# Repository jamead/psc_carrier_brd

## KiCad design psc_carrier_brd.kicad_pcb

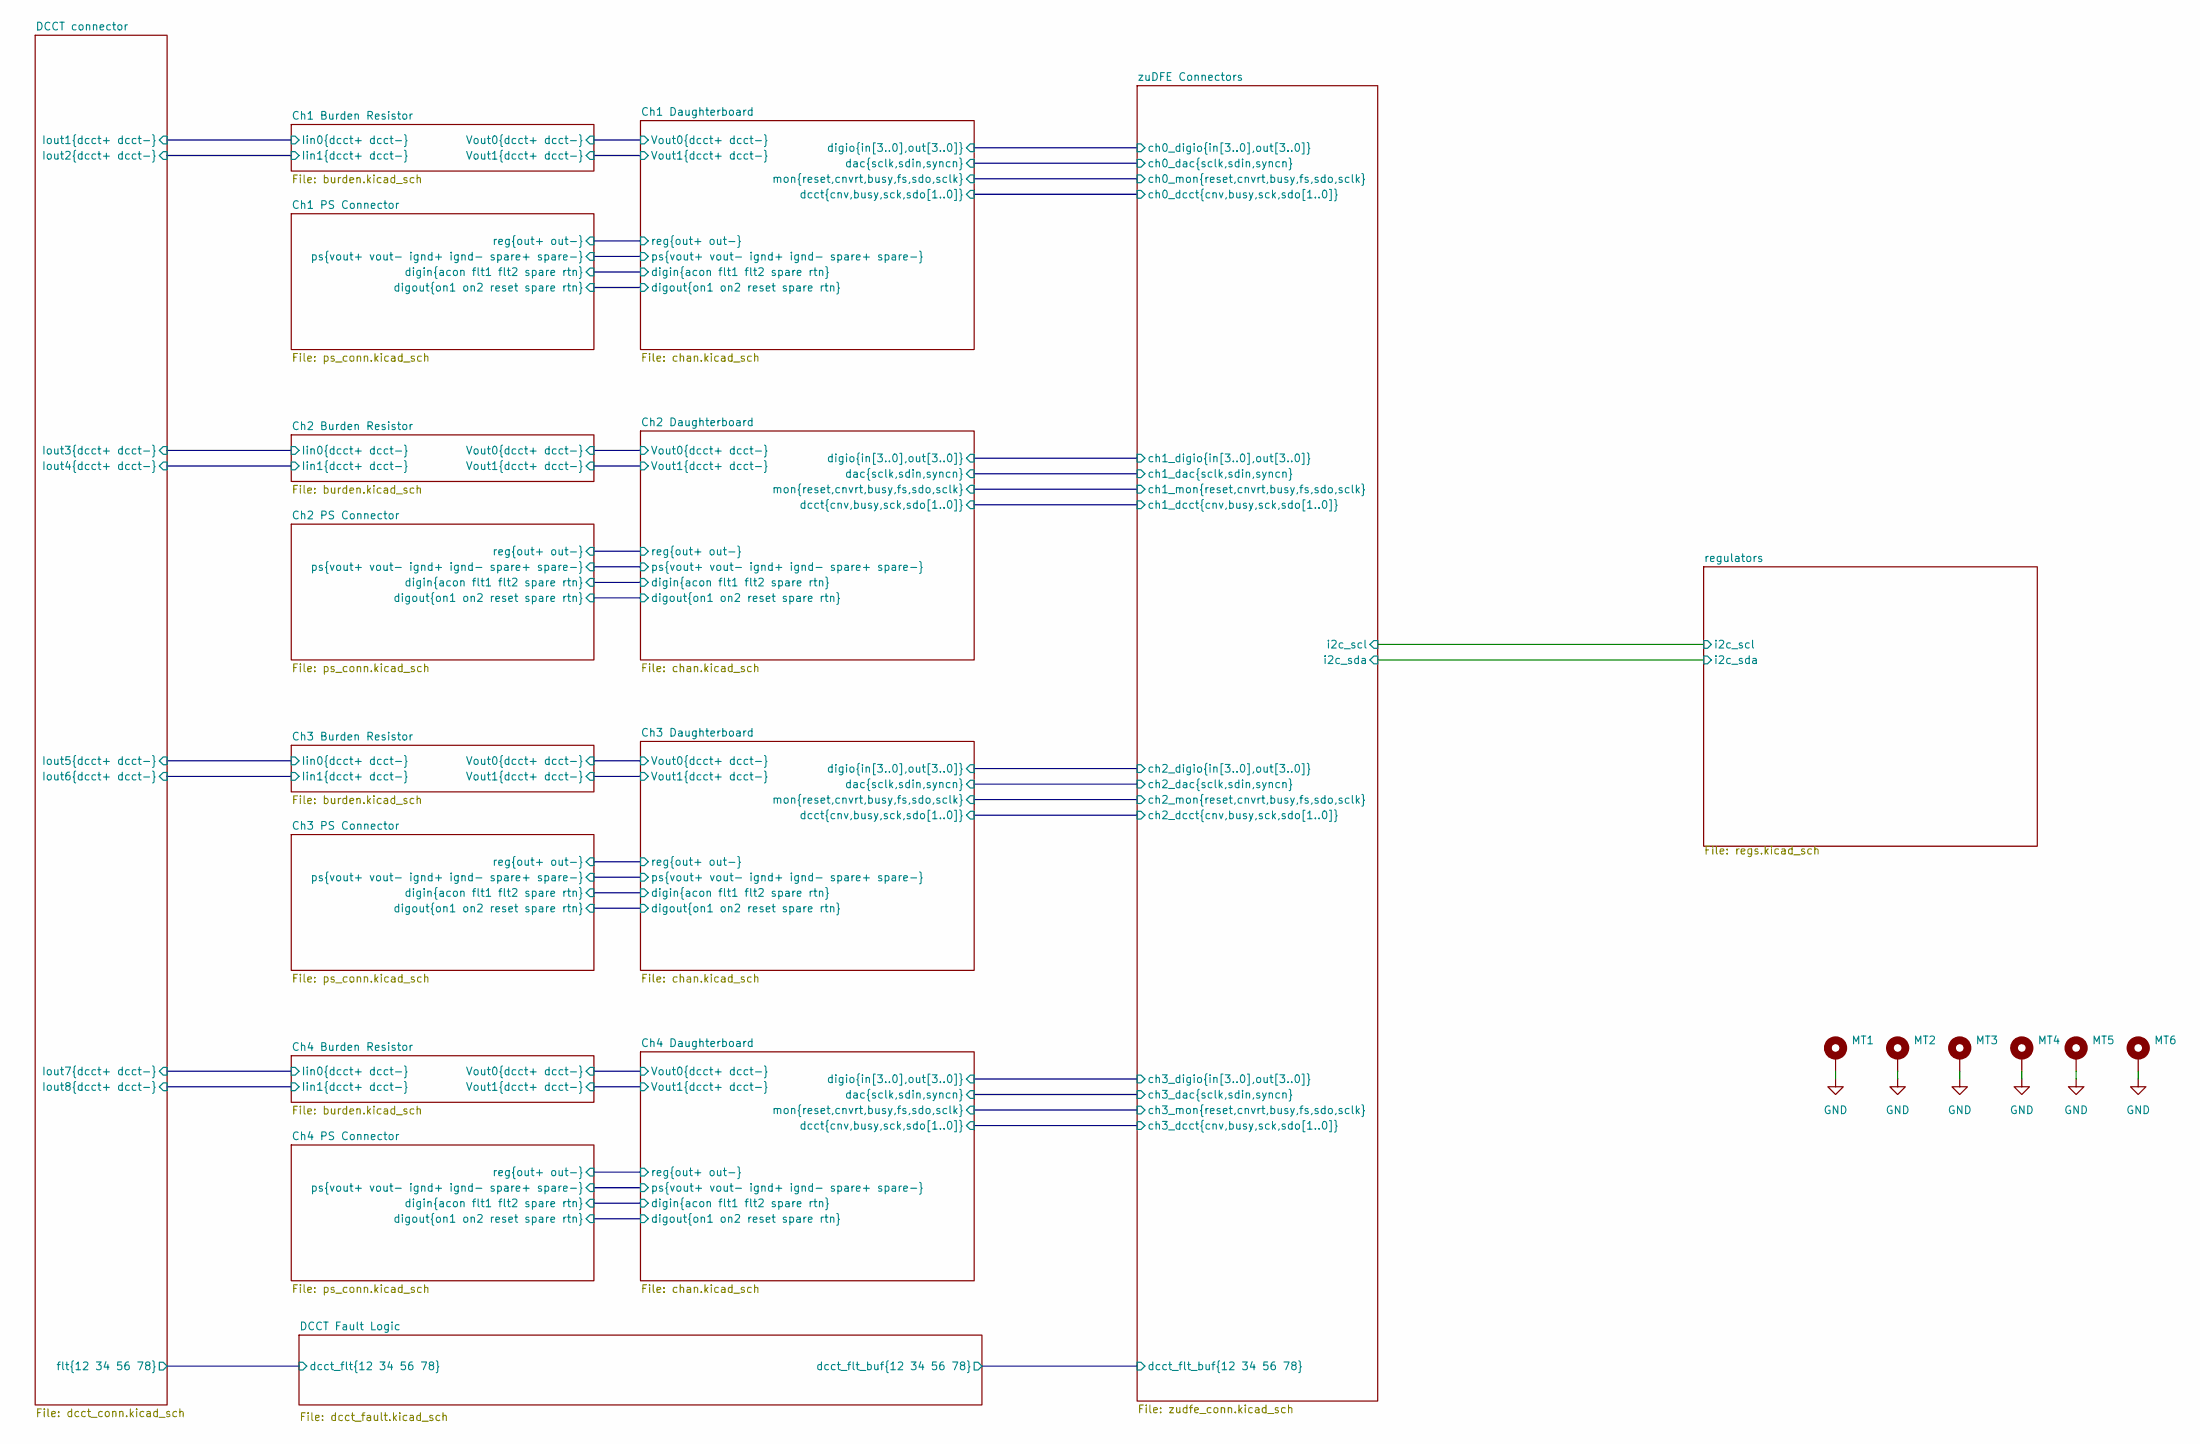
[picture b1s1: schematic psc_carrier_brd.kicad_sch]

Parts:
MT1, MT2, MT3, MT4, MT5, MT6: MountingHole_Pad; MountingHole_4.3mm_M4_DIN965_Pad

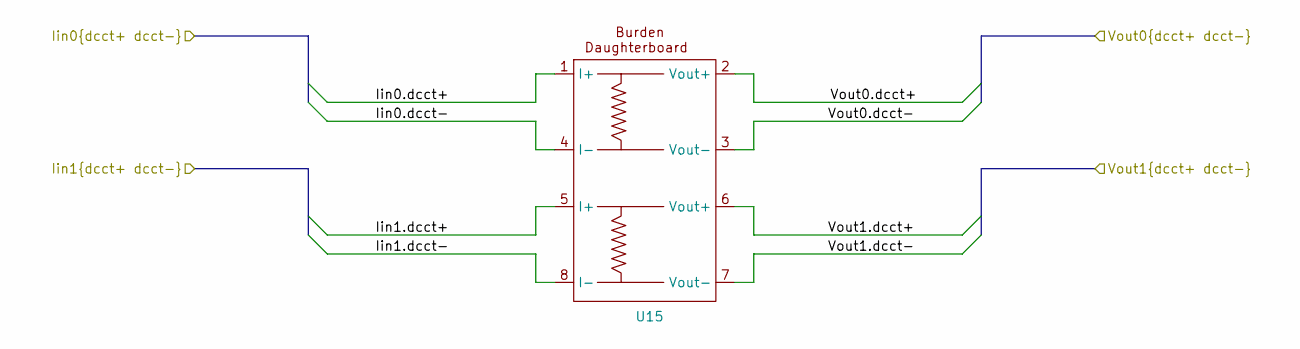
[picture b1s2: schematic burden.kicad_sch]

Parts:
U15: burden

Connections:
/Ch1 Burden Resistor/Iin0.dcct-: U15.4 (I-); also elsewhere on the board

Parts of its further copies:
U16, U17, U18: burden

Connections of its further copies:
/Ch2 Burden Resistor/Iin0.dcct+: U16.1 (I+); also elsewhere on the board
/Ch2 Burden Resistor/Iin0.dcct-: U16.4 (I-); also elsewhere on the board
/Ch2 Burden Resistor/Iin1.dcct+: U16.5 (I+); also elsewhere on the board
/Ch2 Burden Resistor/Iin1.dcct-: U16.8 (I-); also elsewhere on the board
/Ch2 Burden Resistor/Vout0.dcct+: U16.2 (Vout+); also elsewhere on the board
/Ch2 Burden Resistor/Vout0.dcct-: U16.3 (Vout-); also elsewhere on the board
/Ch2 Burden Resistor/Vout1.dcct+: U16.6 (Vout+); also elsewhere on the board
/Ch2 Burden Resistor/Vout1.dcct-: U16.7 (Vout-); also elsewhere on the board
/Ch3 Burden Resistor/Iin0.dcct+: U17.1 (I+); also elsewhere on the board
/Ch3 Burden Resistor/Iin0.dcct-: U17.4 (I-); also elsewhere on the board
/Ch3 Burden Resistor/Iin1.dcct+: U17.5 (I+); also elsewhere on the board
/Ch3 Burden Resistor/Iin1.dcct-: U17.8 (I-); also elsewhere on the board
/Ch3 Burden Resistor/Vout0.dcct+: U17.2 (Vout+); also elsewhere on the board
/Ch3 Burden Resistor/Vout0.dcct-: U17.3 (Vout-); also elsewhere on the board
/Ch3 Burden Resistor/Vout1.dcct+: U17.6 (Vout+); also elsewhere on the board
/Ch3 Burden Resistor/Vout1.dcct-: U17.7 (Vout-); also elsewhere on the board
/Ch4 Burden Resistor/Iin0.dcct+: U18.1 (I+); also elsewhere on the board
/Ch4 Burden Resistor/Iin0.dcct-: U18.4 (I-); also elsewhere on the board
/Ch4 Burden Resistor/Iin1.dcct+: U18.5 (I+); also elsewhere on the board
/Ch4 Burden Resistor/Iin1.dcct-: U18.8 (I-); also elsewhere on the board
/Ch4 Burden Resistor/Vout0.dcct+: U18.2 (Vout+); also elsewhere on the board
/Ch4 Burden Resistor/Vout0.dcct-: U18.3 (Vout-); also elsewhere on the board
/Ch4 Burden Resistor/Vout1.dcct+: U18.6 (Vout+); also elsewhere on the board
/Ch4 Burden Resistor/Vout1.dcct-: U18.7 (Vout-); also elsewhere on the board

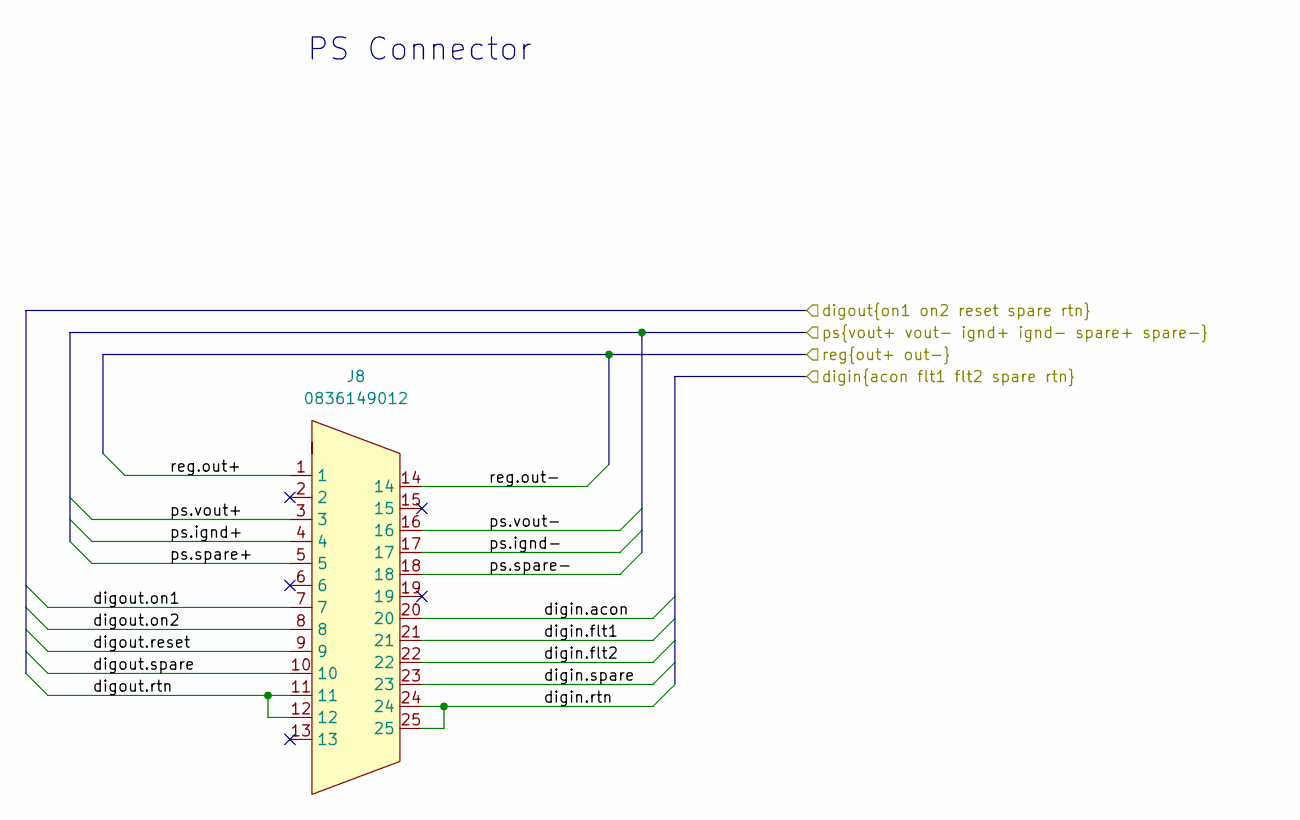
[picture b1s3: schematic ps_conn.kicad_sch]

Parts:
J8: 0836149012

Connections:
/Ch1 Daughterboard/digin.acon: J8.20; also elsewhere on the board
/Ch1 Daughterboard/digin.flt1: J8.21; also elsewhere on the board
/Ch1 Daughterboard/digin.flt2: J8.22; also elsewhere on the board
/Ch1 Daughterboard/digin.rtn: J8.24, J8.25; also elsewhere on the board
/Ch1 Daughterboard/digin.spare: J8.23; also elsewhere on the board
/Ch1 Daughterboard/digout.on1: J8.7; also elsewhere on the board
/Ch1 Daughterboard/digout.on2: J8.8; also elsewhere on the board
/Ch1 Daughterboard/digout.reset: J8.9; also elsewhere on the board
/Ch1 Daughterboard/digout.rtn: J8.11, J8.12; also elsewhere on the board
/Ch1 Daughterboard/digout.spare: J8.10; also elsewhere on the board
/Ch1 Daughterboard/ps.ignd+: J8.4; also elsewhere on the board
/Ch1 Daughterboard/ps.ignd-: J8.17; also elsewhere on the board
/Ch1 Daughterboard/ps.spare+: J8.5; also elsewhere on the board
/Ch1 Daughterboard/ps.spare-: J8.18; also elsewhere on the board
/Ch1 Daughterboard/ps.vout+: J8.3; also elsewhere on the board
/Ch1 Daughterboard/ps.vout-: J8.16; also elsewhere on the board
/Ch1 Daughterboard/reg.out+: J8.1; also elsewhere on the board
/Ch1 Daughterboard/reg.out-: J8.14; also elsewhere on the board

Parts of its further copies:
J11, J14, J17: 0836149012

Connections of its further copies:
/Ch2 Daughterboard/digin.acon: J11.20; also elsewhere on the board
/Ch2 Daughterboard/digin.flt1: J11.21; also elsewhere on the board
/Ch2 Daughterboard/digin.flt2: J11.22; also elsewhere on the board
/Ch2 Daughterboard/digin.rtn: J11.24, J11.25; also elsewhere on the board
/Ch2 Daughterboard/digin.spare: J11.23; also elsewhere on the board
/Ch2 Daughterboard/digout.on1: J11.7; also elsewhere on the board
/Ch2 Daughterboard/digout.on2: J11.8; also elsewhere on the board
/Ch2 Daughterboard/digout.reset: J11.9; also elsewhere on the board
/Ch2 Daughterboard/digout.rtn: J11.11, J11.12; also elsewhere on the board
/Ch2 Daughterboard/digout.spare: J11.10; also elsewhere on the board
/Ch2 Daughterboard/ps.ignd+: J11.4; also elsewhere on the board
/Ch2 Daughterboard/ps.ignd-: J11.17; also elsewhere on the board
/Ch2 Daughterboard/ps.spare+: J11.5; also elsewhere on the board
/Ch2 Daughterboard/ps.spare-: J11.18; also elsewhere on the board
/Ch2 Daughterboard/ps.vout+: J11.3; also elsewhere on the board
/Ch2 Daughterboard/ps.vout-: J11.16; also elsewhere on the board
/Ch2 Daughterboard/reg.out+: J11.1; also elsewhere on the board
/Ch2 Daughterboard/reg.out-: J11.14; also elsewhere on the board
/Ch3 Daughterboard/digin.acon: J14.20; also elsewhere on the board
/Ch3 Daughterboard/digin.flt1: J14.21; also elsewhere on the board
/Ch3 Daughterboard/digin.flt2: J14.22; also elsewhere on the board
/Ch3 Daughterboard/digin.rtn: J14.24, J14.25; also elsewhere on the board
/Ch3 Daughterboard/digin.spare: J14.23; also elsewhere on the board
/Ch3 Daughterboard/digout.on1: J14.7; also elsewhere on the board
/Ch3 Daughterboard/digout.on2: J14.8; also elsewhere on the board
/Ch3 Daughterboard/digout.reset: J14.9; also elsewhere on the board
/Ch3 Daughterboard/digout.rtn: J14.11, J14.12; also elsewhere on the board
/Ch3 Daughterboard/digout.spare: J14.10; also elsewhere on the board
/Ch3 Daughterboard/ps.ignd+: J14.4; also elsewhere on the board
/Ch3 Daughterboard/ps.ignd-: J14.17; also elsewhere on the board
/Ch3 Daughterboard/ps.spare+: J14.5; also elsewhere on the board
/Ch3 Daughterboard/ps.spare-: J14.18; also elsewhere on the board
/Ch3 Daughterboard/ps.vout+: J14.3; also elsewhere on the board
/Ch3 Daughterboard/ps.vout-: J14.16; also elsewhere on the board
/Ch3 Daughterboard/reg.out+: J14.1; also elsewhere on the board
/Ch3 Daughterboard/reg.out-: J14.14; also elsewhere on the board
/Ch4 Daughterboard/digin.acon: J17.20; also elsewhere on the board
/Ch4 Daughterboard/digin.flt1: J17.21; also elsewhere on the board
/Ch4 Daughterboard/digin.flt2: J17.22; also elsewhere on the board
/Ch4 Daughterboard/digin.rtn: J17.24, J17.25; also elsewhere on the board
/Ch4 Daughterboard/digin.spare: J17.23; also elsewhere on the board
/Ch4 Daughterboard/digout.on1: J17.7; also elsewhere on the board
/Ch4 Daughterboard/digout.on2: J17.8; also elsewhere on the board
/Ch4 Daughterboard/digout.reset: J17.9; also elsewhere on the board
/Ch4 Daughterboard/digout.rtn: J17.11, J17.12; also elsewhere on the board
/Ch4 Daughterboard/digout.spare: J17.10; also elsewhere on the board
/Ch4 Daughterboard/ps.ignd+: J17.4; also elsewhere on the board
/Ch4 Daughterboard/ps.ignd-: J17.17; also elsewhere on the board
/Ch4 Daughterboard/ps.spare+: J17.5; also elsewhere on the board
/Ch4 Daughterboard/ps.spare-: J17.18; also elsewhere on the board
/Ch4 Daughterboard/ps.vout+: J17.3; also elsewhere on the board
/Ch4 Daughterboard/ps.vout-: J17.16; also elsewhere on the board
/Ch4 Daughterboard/reg.out+: J17.1; also elsewhere on the board
/Ch4 Daughterboard/reg.out-: J17.14; also elsewhere on the board

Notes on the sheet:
PS Connector

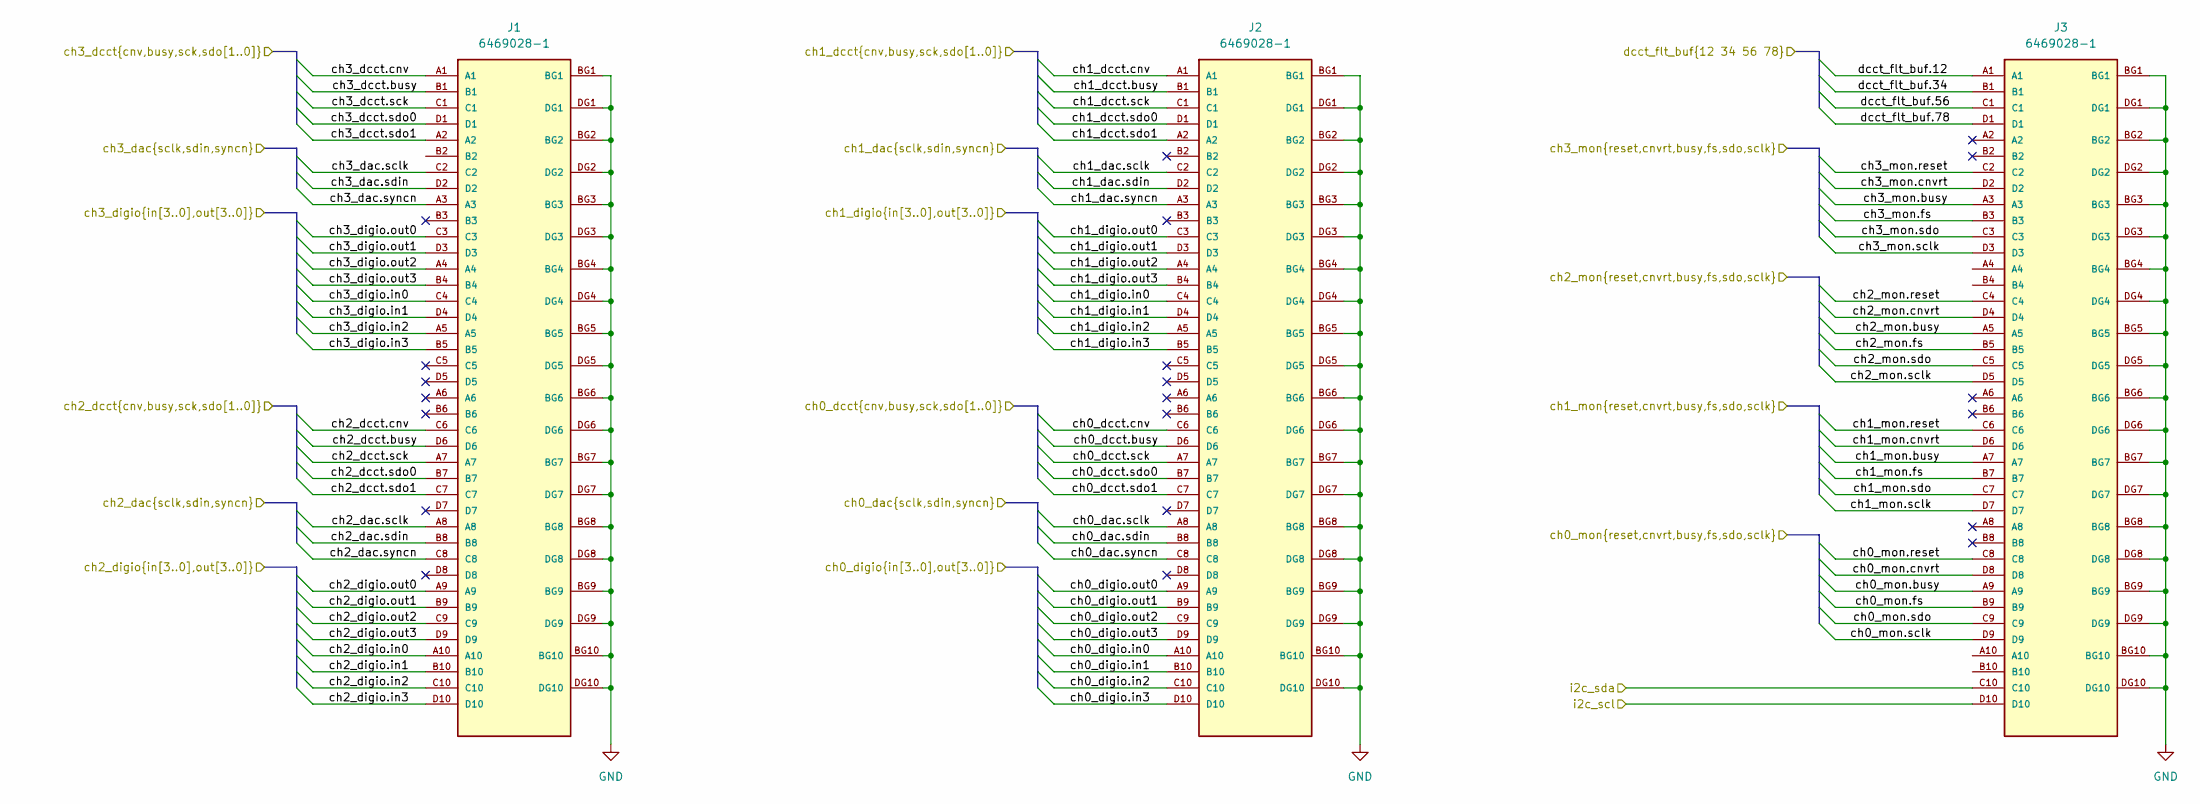
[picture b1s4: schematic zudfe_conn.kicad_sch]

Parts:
J1, J2, J3: 6469028-1; TE_6469028-1; PARTREV E

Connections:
/Ch1 Daughterboard/dac.sclk: J2.A8; also elsewhere on the board
/Ch1 Daughterboard/dac.sdin: J2.B8; also elsewhere on the board
/Ch1 Daughterboard/dac.syncn: J2.C8; also elsewhere on the board
/Ch1 Daughterboard/dcct.busy: J2.D6; also elsewhere on the board
/Ch1 Daughterboard/dcct.cnv: J2.C6; also elsewhere on the board
/Ch1 Daughterboard/dcct.sck: J2.A7; also elsewhere on the board
/Ch1 Daughterboard/dcct.sdo0: J2.B7; also elsewhere on the board
/Ch1 Daughterboard/dcct.sdo1: J2.C7; also elsewhere on the board
/Ch1 Daughterboard/digio.in0: J2.A10; also elsewhere on the board
/Ch1 Daughterboard/digio.in1: J2.B10; also elsewhere on the board
/Ch1 Daughterboard/digio.in2: J2.C10; also elsewhere on the board
/Ch1 Daughterboard/digio.in3: J2.D10; also elsewhere on the board
/Ch1 Daughterboard/digio.out0: J2.A9; also elsewhere on the board
/Ch1 Daughterboard/digio.out1: J2.B9; also elsewhere on the board
/Ch1 Daughterboard/digio.out2: J2.C9; also elsewhere on the board
/Ch1 Daughterboard/digio.out3: J2.D9; also elsewhere on the board
/Ch1 Daughterboard/mon.busy: J3.A9; also elsewhere on the board
/Ch1 Daughterboard/mon.cnvrt: J3.D8; also elsewhere on the board
/Ch1 Daughterboard/mon.fs: J3.B9; also elsewhere on the board
/Ch1 Daughterboard/mon.reset: J3.C8; also elsewhere on the board
/Ch1 Daughterboard/mon.sclk: J3.D9; also elsewhere on the board
/Ch1 Daughterboard/mon.sdo: J3.C9; also elsewhere on the board
/Ch2 Daughterboard/dac.sclk: J2.C2; also elsewhere on the board
/Ch2 Daughterboard/dac.sdin: J2.D2; also elsewhere on the board
/Ch2 Daughterboard/dac.syncn: J2.A3; also elsewhere on the board
/Ch2 Daughterboard/dcct.busy: J2.B1; also elsewhere on the board
/Ch2 Daughterboard/dcct.cnv: J2.A1; also elsewhere on the board
/Ch2 Daughterboard/dcct.sck: J2.C1; also elsewhere on the board
/Ch2 Daughterboard/dcct.sdo0: J2.D1; also elsewhere on the board
/Ch2 Daughterboard/dcct.sdo1: J2.A2; also elsewhere on the board
/Ch2 Daughterboard/digio.in0: J2.C4; also elsewhere on the board
/Ch2 Daughterboard/digio.in1: J2.D4; also elsewhere on the board
/Ch2 Daughterboard/digio.in2: J2.A5; also elsewhere on the board
/Ch2 Daughterboard/digio.in3: J2.B5; also elsewhere on the board
/Ch2 Daughterboard/digio.out0: J2.C3; also elsewhere on the board
/Ch2 Daughterboard/digio.out1: J2.D3; also elsewhere on the board
/Ch2 Daughterboard/digio.out2: J2.A4; also elsewhere on the board
/Ch2 Daughterboard/digio.out3: J2.B4; also elsewhere on the board
/Ch2 Daughterboard/mon.busy: J3.A7; also elsewhere on the board
/Ch2 Daughterboard/mon.cnvrt: J3.D6; also elsewhere on the board
/Ch2 Daughterboard/mon.fs: J3.B7; also elsewhere on the board
/Ch2 Daughterboard/mon.reset: J3.C6; also elsewhere on the board
/Ch2 Daughterboard/mon.sclk: J3.D7; also elsewhere on the board
/Ch2 Daughterboard/mon.sdo: J3.C7; also elsewhere on the board
/Ch3 Daughterboard/dac.sclk: J1.A8; also elsewhere on the board
/Ch3 Daughterboard/dac.sdin: J1.B8; also elsewhere on the board
/Ch3 Daughterboard/dac.syncn: J1.C8; also elsewhere on the board
/Ch3 Daughterboard/dcct.busy: J1.D6; also elsewhere on the board
/Ch3 Daughterboard/dcct.cnv: J1.C6; also elsewhere on the board
/Ch3 Daughterboard/dcct.sck: J1.A7; also elsewhere on the board
/Ch3 Daughterboard/dcct.sdo0: J1.B7; also elsewhere on the board
/Ch3 Daughterboard/dcct.sdo1: J1.C7; also elsewhere on the board
/Ch3 Daughterboard/digio.in0: J1.A10; also elsewhere on the board
/Ch3 Daughterboard/digio.in1: J1.B10; also elsewhere on the board
/Ch3 Daughterboard/digio.in2: J1.C10; also elsewhere on the board
/Ch3 Daughterboard/digio.in3: J1.D10; also elsewhere on the board
/Ch3 Daughterboard/digio.out0: J1.A9; also elsewhere on the board
/Ch3 Daughterboard/digio.out1: J1.B9; also elsewhere on the board
/Ch3 Daughterboard/digio.out2: J1.C9; also elsewhere on the board
/Ch3 Daughterboard/digio.out3: J1.D9; also elsewhere on the board
/Ch3 Daughterboard/mon.busy: J3.A5; also elsewhere on the board
/Ch3 Daughterboard/mon.cnvrt: J3.D4; also elsewhere on the board
/Ch3 Daughterboard/mon.fs: J3.B5; also elsewhere on the board
/Ch3 Daughterboard/mon.reset: J3.C4; also elsewhere on the board
/Ch3 Daughterboard/mon.sclk: J3.D5; also elsewhere on the board
/Ch3 Daughterboard/mon.sdo: J3.C5; also elsewhere on the board
/Ch4 Daughterboard/dac.sclk: J1.C2; also elsewhere on the board
/Ch4 Daughterboard/dac.sdin: J1.D2; also elsewhere on the board
/Ch4 Daughterboard/dac.syncn: J1.A3; also elsewhere on the board
/Ch4 Daughterboard/dcct.busy: J1.B1; also elsewhere on the board
/Ch4 Daughterboard/dcct.cnv: J1.A1; also elsewhere on the board
/Ch4 Daughterboard/dcct.sck: J1.C1; also elsewhere on the board
/Ch4 Daughterboard/dcct.sdo0: J1.D1; also elsewhere on the board
/Ch4 Daughterboard/dcct.sdo1: J1.A2; also elsewhere on the board
/Ch4 Daughterboard/digio.in0: J1.C4; also elsewhere on the board
/Ch4 Daughterboard/digio.in1: J1.D4; also elsewhere on the board
/Ch4 Daughterboard/digio.in2: J1.A5; also elsewhere on the board
/Ch4 Daughterboard/digio.in3: J1.B5; also elsewhere on the board
/Ch4 Daughterboard/digio.out0: J1.C3; also elsewhere on the board
/Ch4 Daughterboard/digio.out1: J1.D3; also elsewhere on the board
/Ch4 Daughterboard/digio.out2: J1.A4; also elsewhere on the board
/Ch4 Daughterboard/digio.out3: J1.B4; also elsewhere on the board
/Ch4 Daughterboard/mon.busy: J3.A3; also elsewhere on the board
/Ch4 Daughterboard/mon.cnvrt: J3.D2; also elsewhere on the board
/Ch4 Daughterboard/mon.fs: J3.B3; also elsewhere on the board
/Ch4 Daughterboard/mon.reset: J3.C2; also elsewhere on the board
/Ch4 Daughterboard/mon.sclk: J3.D3; also elsewhere on the board
/Ch4 Daughterboard/mon.sdo: J3.C3; also elsewhere on the board
/DCCT Fault Logic/dcct_flt_buf.12: J3.A1; also elsewhere on the board
/DCCT Fault Logic/dcct_flt_buf.34: J3.B1; also elsewhere on the board
/DCCT Fault Logic/dcct_flt_buf.56: J3.C1; also elsewhere on the board
/DCCT Fault Logic/dcct_flt_buf.78: J3.D1; also elsewhere on the board
/regulators/i2c_scl: J3.D10; also elsewhere on the board
/regulators/i2c_sda: J3.C10; also elsewhere on the board
